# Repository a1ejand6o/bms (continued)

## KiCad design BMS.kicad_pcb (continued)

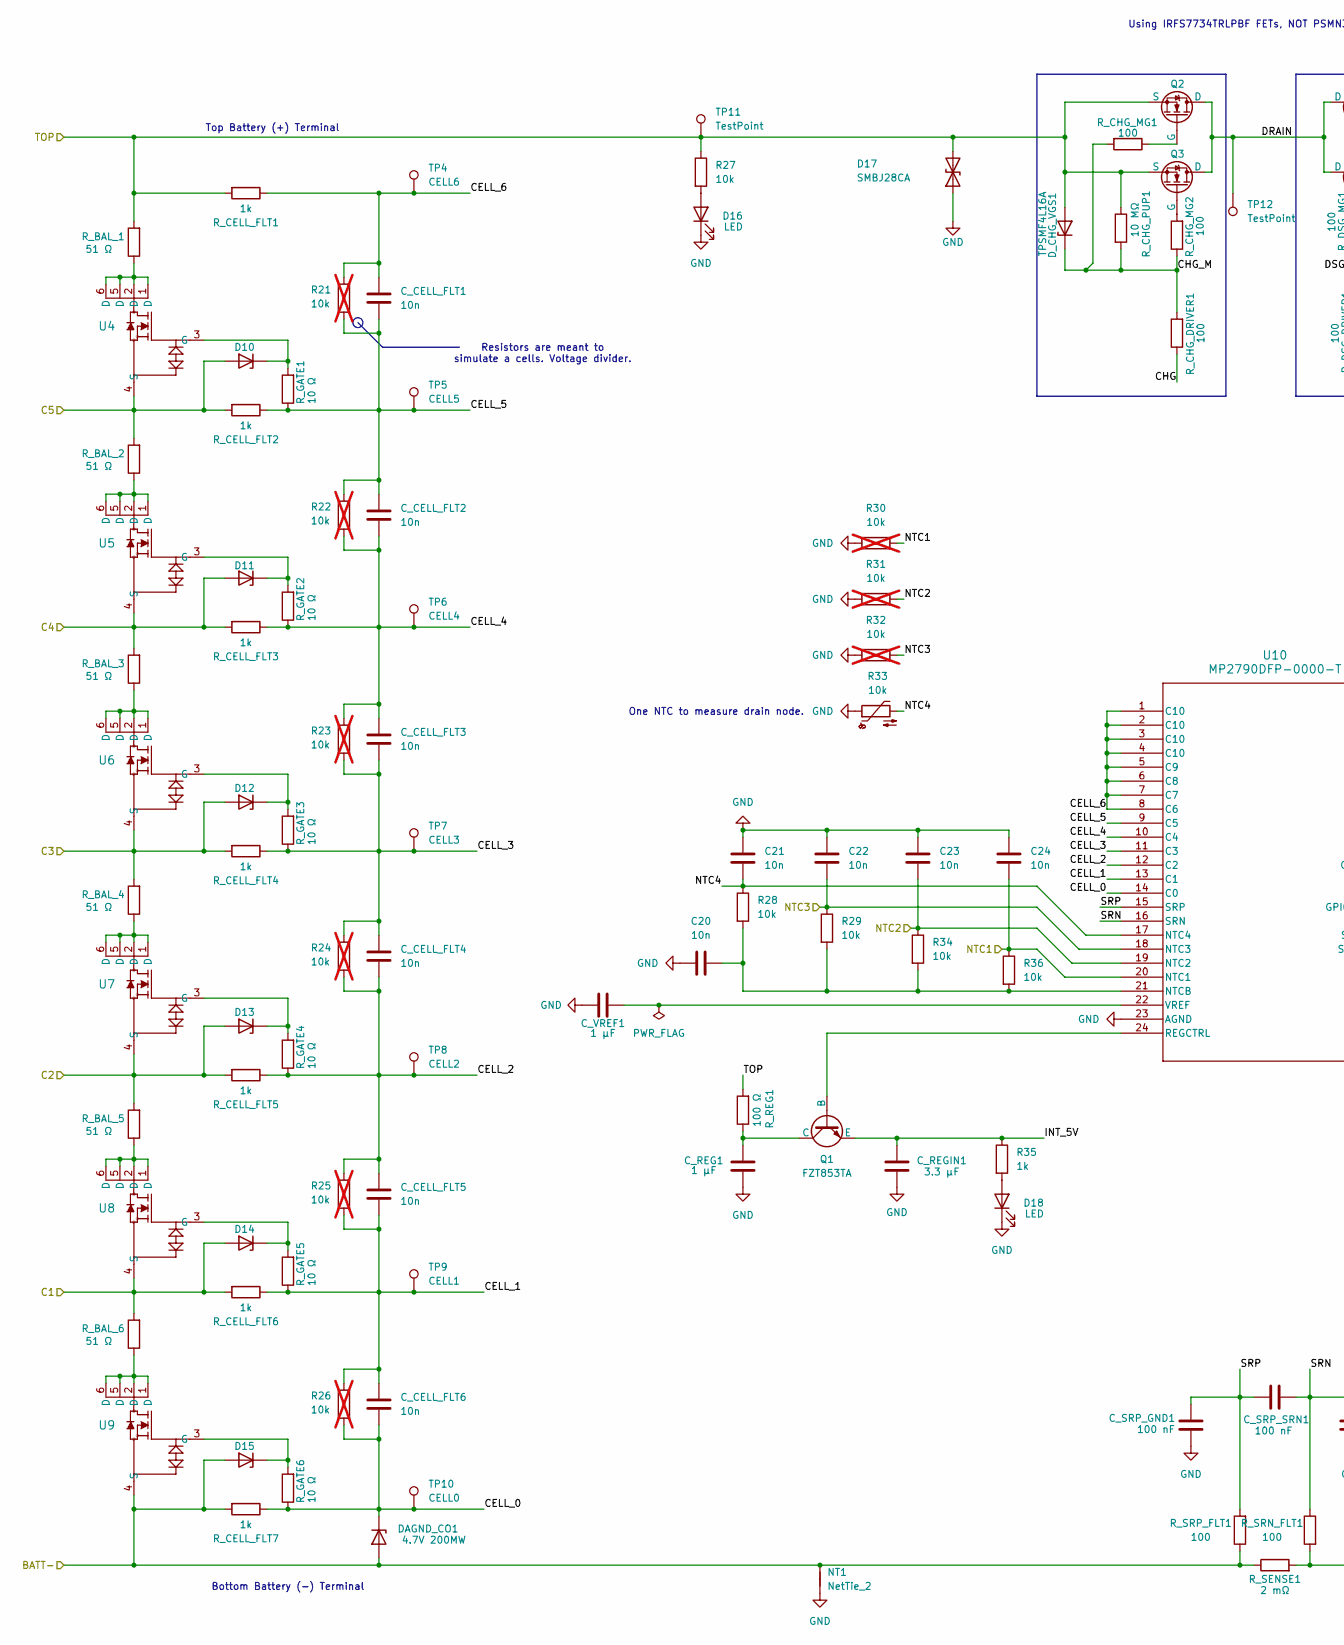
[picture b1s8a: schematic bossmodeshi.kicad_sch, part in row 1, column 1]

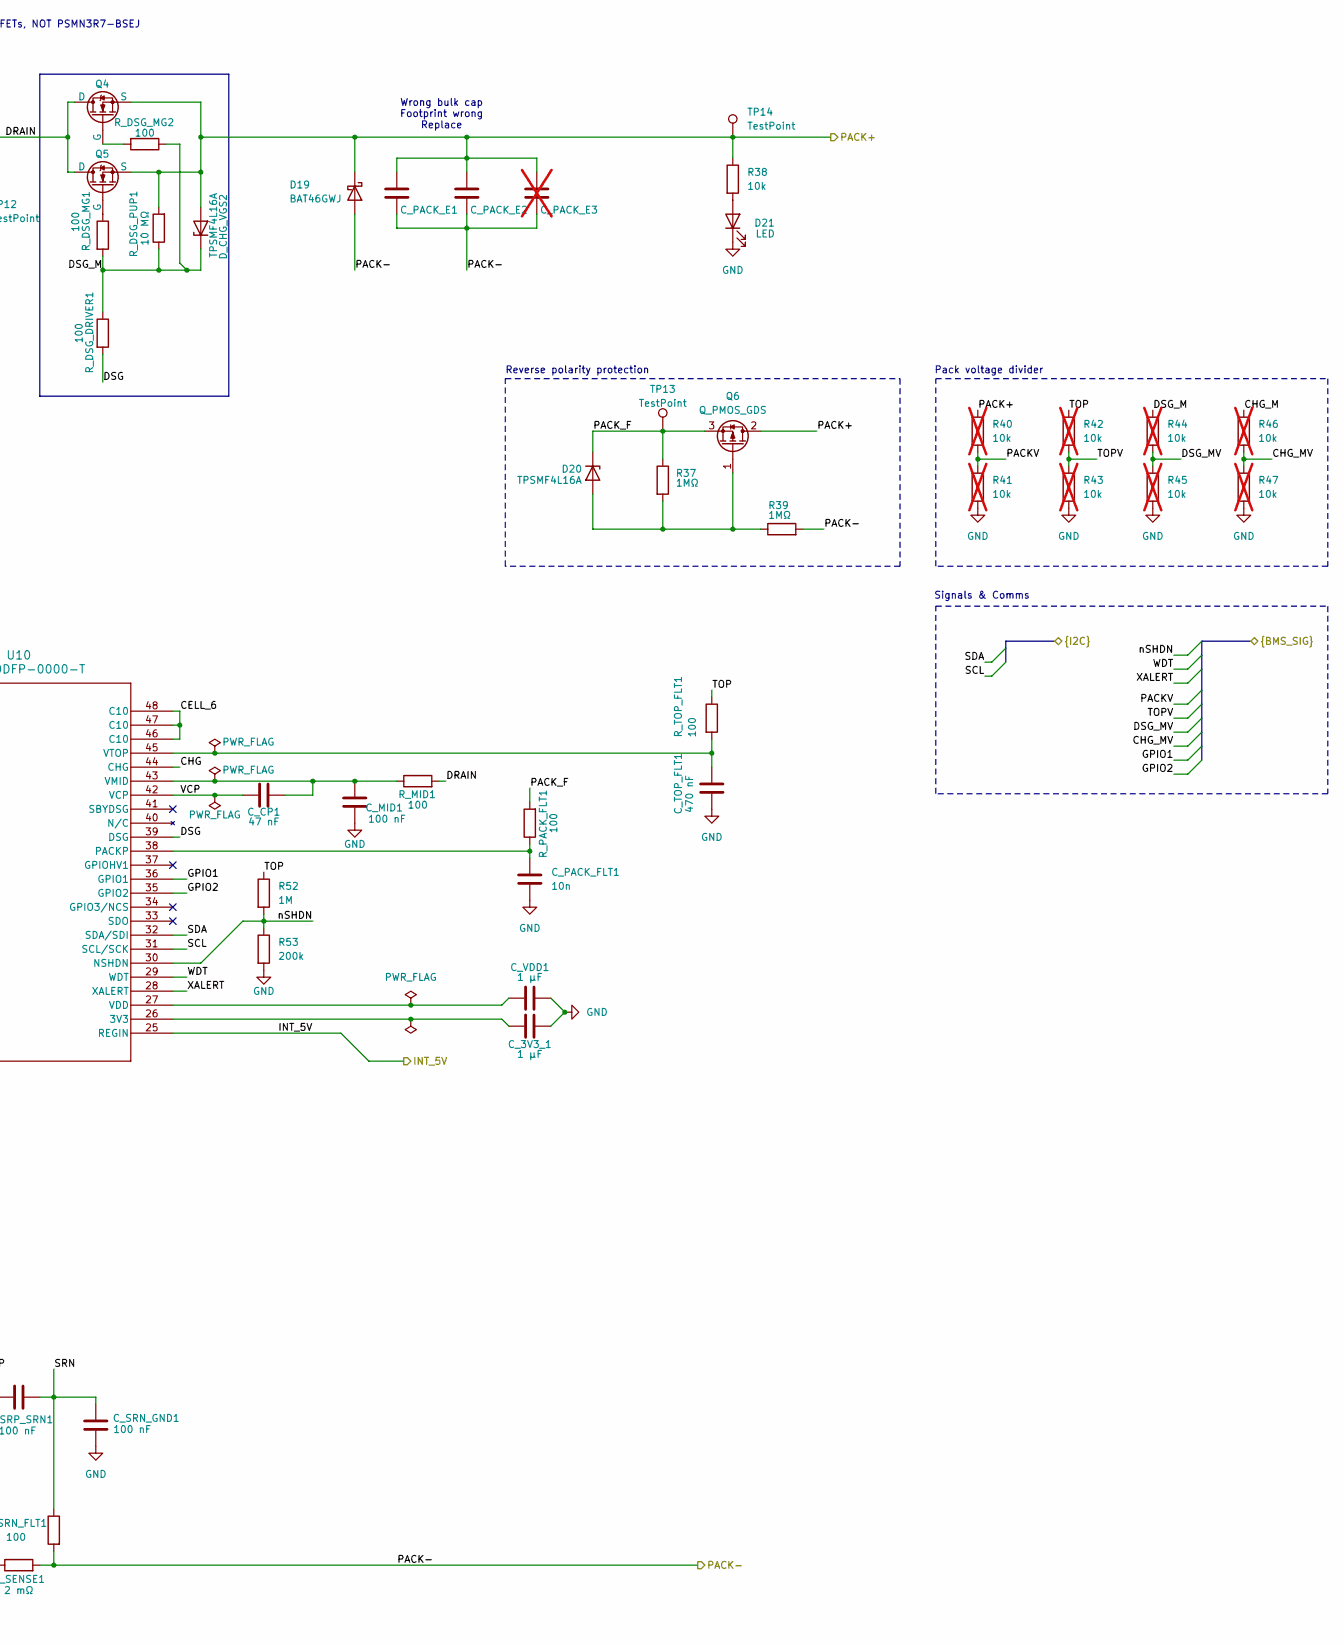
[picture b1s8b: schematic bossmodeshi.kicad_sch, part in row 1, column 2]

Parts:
C20, C21, C22, C23, C24: 10n; C_0603_1608Metric; Mfr P/N GRT1885C1E103FA02D
C_3V3_1: 1 μF; C_0603_1608Metric; Mfr P/N GCM188D71H105KE36J
C_CELL_FLT1, C_CELL_FLT2, C_CELL_FLT3, C_CELL_FLT4, C_CELL_FLT5, C_CELL_FLT6: 10n; C_0603_1608Metric; Mfr P/N GRT1885C1E103FA02D
C_CP1: 47 nF; C_0603_1608Metric; Mfr P/N CC0603JRX7R9BB473
C_MID1: 100 nF; C_0603_1608Metric; Mfr P/N CC0603JRX7R9BB104
C_PACK_E1, C_PACK_E2: C_1206_3216Metric
C_PACK_E3: C_1206_3216Metric; not fitted
C_PACK_FLT1: 10n; C_0603_1608Metric; Mfr P/N GRT1885C1E103FA02D
C_REG1: 1 μF; C_0603_1608Metric; Mfr P/N GCM188D71H105KE36J
C_REGIN1: 3.3 μF; C_0603_1608Metric; Mfr P/N C1608X5R1E335KT000E
C_SRN_GND1: 100 nF; C_0603_1608Metric; Mfr P/N CC0603JRX7R9BB104
C_SRP_GND1: 100 nF; C_0603_1608Metric; Mfr P/N CC0603JRX7R9BB104
C_SRP_SRN1: 100 nF; C_0603_1608Metric; Mfr P/N CC0603JRX7R9BB104
C_TOP_FLT1: 470 nF; C_0603_1608Metric; Mfr P/N CC0603KRX7R9BB474
C_VDD1: 1 μF; C_0603_1608Metric; Mfr P/N GCM188D71H105KE36J
C_VREF1: 1 μF; C_0603_1608Metric; Mfr P/N GCM188D71H105KE36J
D10, D11, D12, D13, D14, D15: PTVS5V0S1UR,115; Nexperia_CFP3_SOD-123W; Mfr P/N PTVS5V0S1UR,115
D16, D21: LED; LED_0603_1608Metric; Mfr P/N SML-310LTT86
D17: SMBJ28CA; D_SMB; Mfr P/N SMBJ28CA
D18: LED; LED_0603_1608Metric; Mfr P/N SML-E12P8WT86
D19: BAT46GWJ; D_SOD-123; Mfr P/N BAT46W-E3-18
D20: TPSMF4L16A; Nexperia_CFP3_SOD-123W; Mfr P/N TPSMF4L16A
DAGND_CO1: 4.7V 200MW; D_SOD-323; Mfr P/N BZT52C4V7S-7-F
D_CHG_VGS1, D_CHG_VGS2: TPSMF4L16A; Nexperia_CFP3_SOD-123W; Mfr P/N TPSMF4L16A
NT1: NetTie_2; NetTie-2_SMD_Pad2.0mm
Q1: FZT853TA; SOT230P700X185-4N; Mfr P/N FZT853TA
Q2, Q3, Q4, Q5: PSMN3R7-100BSE; TO-263-2; Mfr P/N PSMN3R7-100BSEJ
Q6: Q_PMOS_GDS; SOT-23; Mfr P/N SI01P10-TP
R21, R22, R23, R24, R25, R26, R40, R41, R42, R43, R44, R45, R46, R47: 10k; R_0603_1608Metric; Mfr P/N RC0603FR-0710KL; not fitted
R27, R28, R29, R34, R36, R38: 10k; R_0603_1608Metric; Mfr P/N RC0603FR-0710KL
R30, R31, R32: 10k; R_0603_1608Metric; not fitted
R33: 10k; R_0603_1608Metric; Mfr P/N NTCS0603E3103FLT
R35: 1k; R_0603_1608Metric; Mfr P/N AC0603FR-071KL
R37, R39: 1MΩ; R_0603_1608Metric; Mfr P/N RC0603FR-071ML
R52: 1M; R_0603_1608Metric; Mfr P/N 0603WAF1004T5E
R53: 200k; R_0603_1608Metric; Mfr P/N 0603WAF2003T5E
R_BAL_1, R_BAL_2, R_BAL_3, R_BAL_4, R_BAL_5, R_BAL_6: 51 Ω; R_1206_3216Metric; Mfr P/N SR1206FR-7W51RL
R_CELL_FLT1, R_CELL_FLT2, R_CELL_FLT3, R_CELL_FLT4, R_CELL_FLT5, R_CELL_FLT6, R_CELL_FLT7: 1k; R_0603_1608Metric; Mfr P/N AC0603FR-071KL
R_CHG_DRIVER1: 100; R_0603_1608Metric; Mfr P/N CRCW0603100RFKEAHP
R_CHG_MG1, R_CHG_MG2: 100; R_0603_1608Metric; Mfr P/N CRCW0603100RFKEAHP
R_CHG_PUP1: 10 MΩ; R_0603_1608Metric; Mfr P/N 0603WAF1005T5E
R_DSG_DRIVER1: 100; R_0603_1608Metric; Mfr P/N CRCW0603100RFKEAHP
R_DSG_MG1, R_DSG_MG2: 100; R_0603_1608Metric; Mfr P/N CRCW0603100RFKEAHP
R_DSG_PUP1: 10 MΩ; R_0603_1608Metric; Mfr P/N 0603WAF1005T5E
R_GATE1, R_GATE2, R_GATE3, R_GATE4, R_GATE5, R_GATE6: 10 Ω; R_0603_1608Metric; Mfr P/N CRCW060310R0FKEAHP
R_MID1: 100; R_0603_1608Metric; Mfr P/N CRCW0603100RFKEAHP
R_PACK_FLT1: 100; R_0603_1608Metric; Mfr P/N CRCW0603100RFKEAHP
R_REG1: 100 Ω; R_2512_6332Metric; Mfr P/N 25121WJ0101T4E
R_SENSE1: 2 mΩ; R_2512_6332Metric; Mfr P/N PA2512FKE7W0R002E
R_SRN_FLT1: 100; R_0603_1608Metric; Mfr P/N CRCW0603100RFKEAHP
R_SRP_FLT1: 100; R_0603_1608Metric; Mfr P/N CRCW0603100RFKEAHP
R_TOP_FLT1: 100; R_0603_1608Metric; Mfr P/N CRCW0603100RFKEAHP
TP4: CELL6; Harwin TP; Mfr P/N S2761-46R
TP5: CELL5; Harwin TP; Mfr P/N S2761-46R
TP6: CELL4; Harwin TP; Mfr P/N S2761-46R
TP7: CELL3; Harwin TP; Mfr P/N S2761-46R
TP8: CELL2; Harwin TP; Mfr P/N S2761-46R
TP9: CELL1; Harwin TP; Mfr P/N S2761-46R
TP10: CELL0; Harwin TP; Mfr P/N S2761-46R
TP11, TP12, TP13, TP14: TestPoint; Harwin TP; Mfr P/N S2761-46R
U4, U5, U6, U7, U8, U9: SQ1464EEH-T1_GE3; SC_4EEH-T1_GE3_VIS; Mfr P/N SQ1464EEH-T1_GE3
U10: MP2790DFP-0000-T; TQFP-48_MP2790_MNP; Mfr P/N MP2790DFP-0000-T

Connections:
/main/BMS/BATT-: D15.2 (A), DAGND_CO1.2 (A), NT1.2, R_CELL_FLT7.2, R_SENSE1.1, R_SRP_FLT1.1, U9.4 (S); also elsewhere on the board
/main/BMS/C1: D14.2 (A), R_BAL_6.2, R_CELL_FLT6.2, U8.4 (S); also elsewhere on the board
/main/BMS/C2: D13.2 (A), R_BAL_5.2, R_CELL_FLT5.2, U7.4 (S); also elsewhere on the board
/main/BMS/C3: D12.2 (A), R_BAL_4.2, R_CELL_FLT4.2, U6.4 (S); also elsewhere on the board
/main/BMS/C4: D11.2 (A), R_BAL_3.2, R_CELL_FLT3.2, U5.4 (S); also elsewhere on the board
/main/BMS/C5: D10.2 (A), R_BAL_2.2, R_CELL_FLT2.2, U4.4 (S); also elsewhere on the board
/main/BMS/CELL_0: C_CELL_FLT6.2, DAGND_CO1.1 (K), R26.2, R_CELL_FLT7.1, R_GATE6.1, TP10.1, U10.14 (C0)
/main/BMS/CELL_1: C_CELL_FLT5.2, C_CELL_FLT6.1, R25.2, R26.1, R_CELL_FLT6.1, R_GATE5.1, TP9.1, U10.13 (C1)
/main/BMS/CELL_2: C_CELL_FLT4.2, C_CELL_FLT5.1, R24.2, R25.1, R_CELL_FLT5.1, R_GATE4.1, TP8.1, U10.12 (C2)
/main/BMS/CELL_3: C_CELL_FLT3.2, C_CELL_FLT4.1, R23.2, R24.1, R_CELL_FLT4.1, R_GATE3.1, TP7.1, U10.11 (C3)
/main/BMS/CELL_4: C_CELL_FLT2.2, C_CELL_FLT3.1, R22.2, R23.1, R_CELL_FLT3.1, R_GATE2.1, TP6.1, U10.10 (C4)
/main/BMS/CELL_5: C_CELL_FLT1.2, C_CELL_FLT2.1, R21.2, R22.1, R_CELL_FLT2.1, R_GATE1.1, TP5.1, U10.9 (C5)
/main/BMS/CELL_6: C_CELL_FLT1.1, R21.1, R_CELL_FLT1.1, TP4.1, U10.1 (C10), U10.2 (C10), U10.3 (C10), U10.4 (C10), U10.5 (C9), U10.6 (C8), U10.7 (C7), U10.8 (C6), U10.46 (C10), U10.47 (C10), U10.48 (C10)
/main/BMS/CHG: R_CHG_DRIVER1.1, U10.44 (CHG)
/main/BMS/CHG_M: D_CHG_VGS1.1 (K), R46.1, R_CHG_DRIVER1.2, R_CHG_MG1.2, R_CHG_MG2.1, R_CHG_PUP1.2
/main/BMS/DRAIN: Q2.1 (D), Q3.1 (D), Q4.1 (D), Q5.1 (D), R_MID1.2, TP12.1
/main/BMS/DSG: R_DSG_DRIVER1.2, U10.39 (DSG)
/main/BMS/DSG_M: D_CHG_VGS2.1 (K), R44.1, R_DSG_DRIVER1.1, R_DSG_MG1.2, R_DSG_MG2.1, R_DSG_PUP1.1
/main/BMS/NTC1: C24.1, R30.2, R36.1, U10.20 (NTC1); also elsewhere on the board
/main/BMS/NTC2: C23.1, R31.2, R34.1, U10.19 (NTC2); also elsewhere on the board
/main/BMS/NTC3: C22.1, R29.1, R32.2, U10.18 (NTC3); also elsewhere on the board
/main/BMS/NTC4: C21.2, R28.1, R33.2, U10.17 (NTC4)
/main/BMS/PACK-: C_PACK_E1.2, C_PACK_E2.2, C_PACK_E3.2, D19.2 (A), R39.2, R_SENSE1.2, R_SRN_FLT1.2; also elsewhere on the board
/main/BMS/PACK_F: D20.1 (K), Q6.3 (S), R37.1, R_PACK_FLT1.2, TP13.1
/main/BMS/SCL: U10.31 (SCL/SCK); also elsewhere on the board
/main/BMS/SDA: U10.32 (SDA/SDI); also elsewhere on the board
/main/BMS/SRN: C_SRN_GND1.2, C_SRP_SRN1.1, R_SRN_FLT1.1, U10.16 (SRN)
/main/BMS/SRP: C_SRP_GND1.1, C_SRP_SRN1.2, R_SRP_FLT1.2, U10.15 (SRP)
/main/BMS/TOP: D17.2 (A2), D_CHG_VGS1.2 (A), Q2.3 (S), Q3.3 (S), R27.1, R42.1, R52.1, R_BAL_1.2, R_CELL_FLT1.2, R_CHG_PUP1.1, R_REG1.2, R_TOP_FLT1.1, TP11.1; also elsewhere on the board
/main/BMS/VCP: C_CP1.1, U10.42 (VCP)
/main/GPIO1: U10.36 (GPIO1); also elsewhere on the board
/main/GPIO2: U10.35 (GPIO2); also elsewhere on the board
/main/INT_5V: C_REGIN1.2, Q1.3 (E), R35.1, U10.25 (REGIN); also elsewhere on the board
/main/PACK+: C_PACK_E1.1, C_PACK_E2.1, C_PACK_E3.1, D19.1 (K), D_CHG_VGS2.2 (A), Q4.3 (S), Q5.3 (S), Q6.2 (D), R38.1, R40.1, R_DSG_PUP1.2, TP14.1; also elsewhere on the board
/main/WDT: U10.29 (WDT); also elsewhere on the board
/main/XALERT: U10.28 (XALERT); also elsewhere on the board
/main/nSHDN: R52.2, R53.1, U10.30 (NSHDN); also elsewhere on the board
GND: C20.1, C21.1, C22.2, C23.2, C24.2, C_3V3_1.1, C_MID1.2, C_PACK_FLT1.2, C_REG1.2, C_REGIN1.1, C_SRN_GND1.1, C_SRP_GND1.2, C_TOP_FLT1.2, C_VDD1.2, C_VREF1.2, D16.1 (K), D17.1 (A1), D18.1 (K), D21.1 (K), NT1.1, R30.1, R31.1, R32.1, R33.1, R41.2, R43.2, R45.2, R47.2, R53.2, U10.23 (AGND); also elsewhere on the board
unnamed: D10.1 (K), R_GATE1.2, U4.3 (G)
unnamed: D11.1 (K), R_GATE2.2, U5.3 (G)
unnamed: D12.1 (K), R_GATE3.2, U6.3 (G)
unnamed: D13.1 (K), R_GATE4.2, U7.3 (G)
unnamed: D14.1 (K), R_GATE5.2, U8.3 (G)
unnamed: D15.1 (K), R_GATE6.2, U9.3 (G)
unnamed: D16.2 (A), R27.2
unnamed: D18.2 (A), R35.2
unnamed: D20.2 (A), Q6.1 (G), R37.2, R39.1
unnamed: D21.2 (A), R38.2
unnamed: Q1.2 (B), U10.24 (REGCTRL)
unnamed: C_REG1.1, Q1.1 (C), R_REG1.1
unnamed: Q2.2 (G), R_CHG_MG1.1
unnamed: Q3.2 (G), R_CHG_MG2.2
unnamed: Q4.2 (G), R_DSG_MG2.2
unnamed: Q5.2 (G), R_DSG_MG1.1
unnamed: R40.2, R41.1
unnamed: R42.2, R43.1
unnamed: R44.2, R45.1
unnamed: R46.2, R47.1
unnamed: R_BAL_1.1, U4.1 (D), U4.2 (D), U4.5 (D), U4.6 (D)
unnamed: R_BAL_2.1, U5.1 (D), U5.2 (D), U5.5 (D), U5.6 (D)
unnamed: R_BAL_3.1, U6.1 (D), U6.2 (D), U6.5 (D), U6.6 (D)
unnamed: R_BAL_4.1, U7.1 (D), U7.2 (D), U7.5 (D), U7.6 (D)
unnamed: R_BAL_5.1, U8.1 (D), U8.2 (D), U8.5 (D), U8.6 (D)
unnamed: R_BAL_6.1, U9.1 (D), U9.2 (D), U9.5 (D), U9.6 (D)
unnamed: C_3V3_1.2, U10.26 (3V3)
unnamed: C20.2, R28.2, R29.2, R34.2, R36.2, U10.21 (NTCB)
unnamed: C_PACK_FLT1.1, R_PACK_FLT1.1, U10.38 (PACKP)
unnamed: C_VDD1.1, U10.27 (VDD)
unnamed: C_CP1.2, C_MID1.1, R_MID1.1, U10.43 (VMID)
unnamed: C_VREF1.1, U10.22 (VREF)
unnamed: C_TOP_FLT1.1, R_TOP_FLT1.2, U10.45 (VTOP)

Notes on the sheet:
Using IRFS7734TRLPBF FETs, NOT PSMN3R7-BSEJ
Resistors are meant to simulate a cells. Voltage divider.
Footprint wrong Replace
Reverse polarity protection
Pack voltage divider
Top Battery (+) Terminal
Wrong bulk cap
Signals & Comms
Bottom Battery (-) Terminal
One NTC to measure drain node.

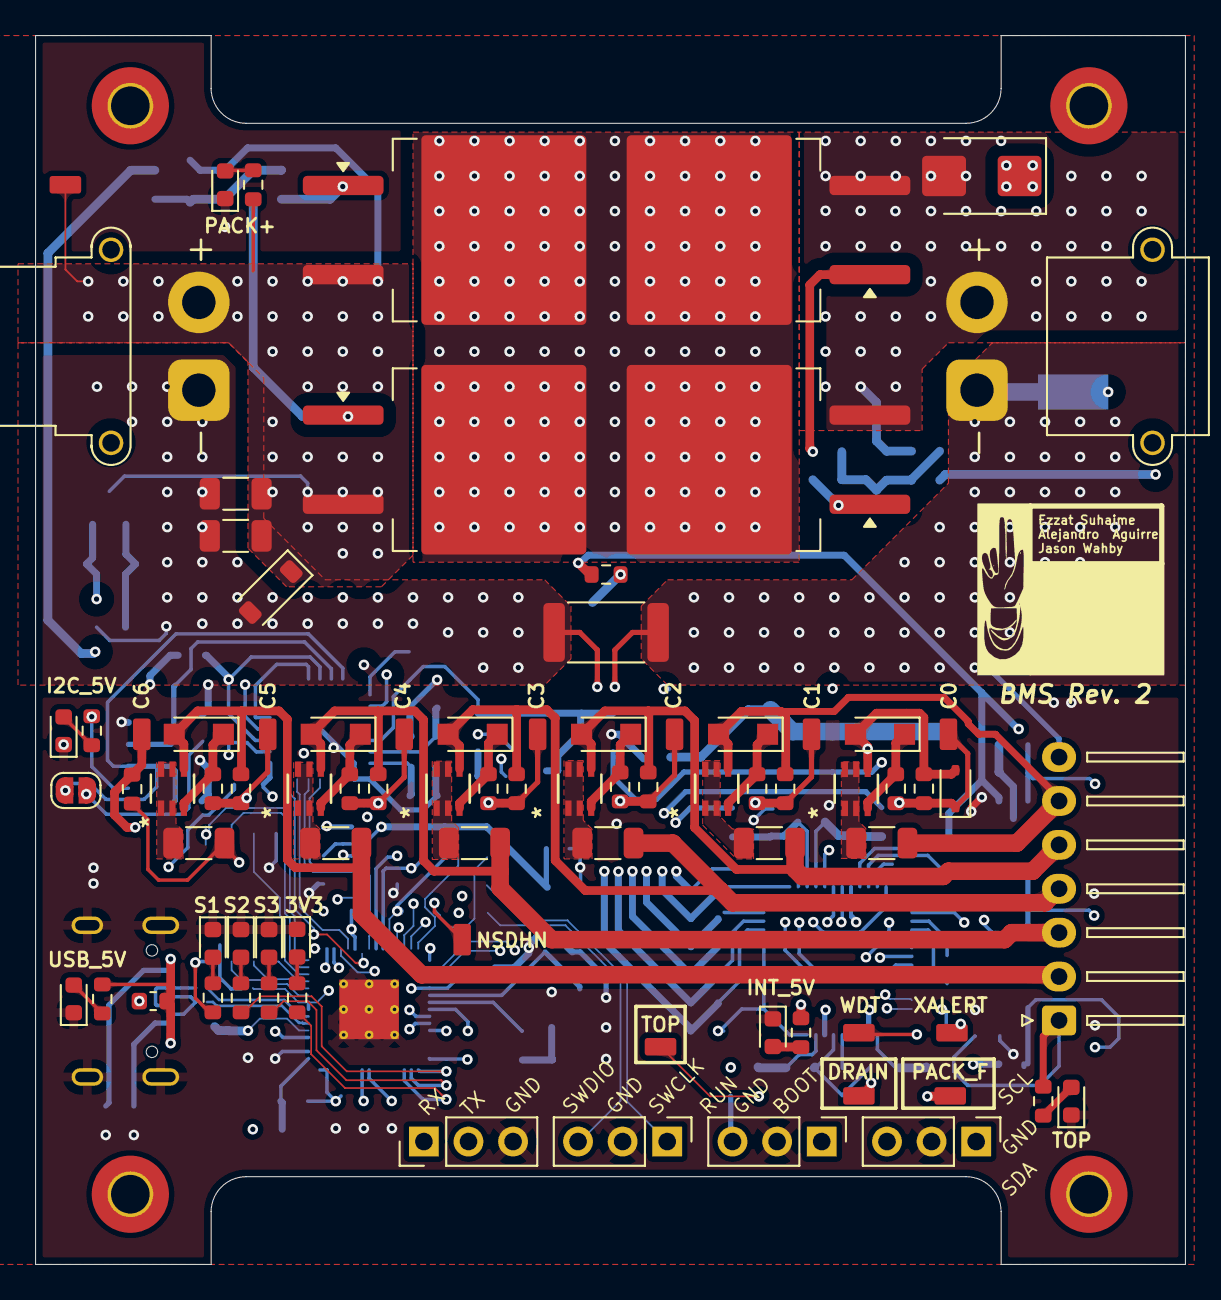
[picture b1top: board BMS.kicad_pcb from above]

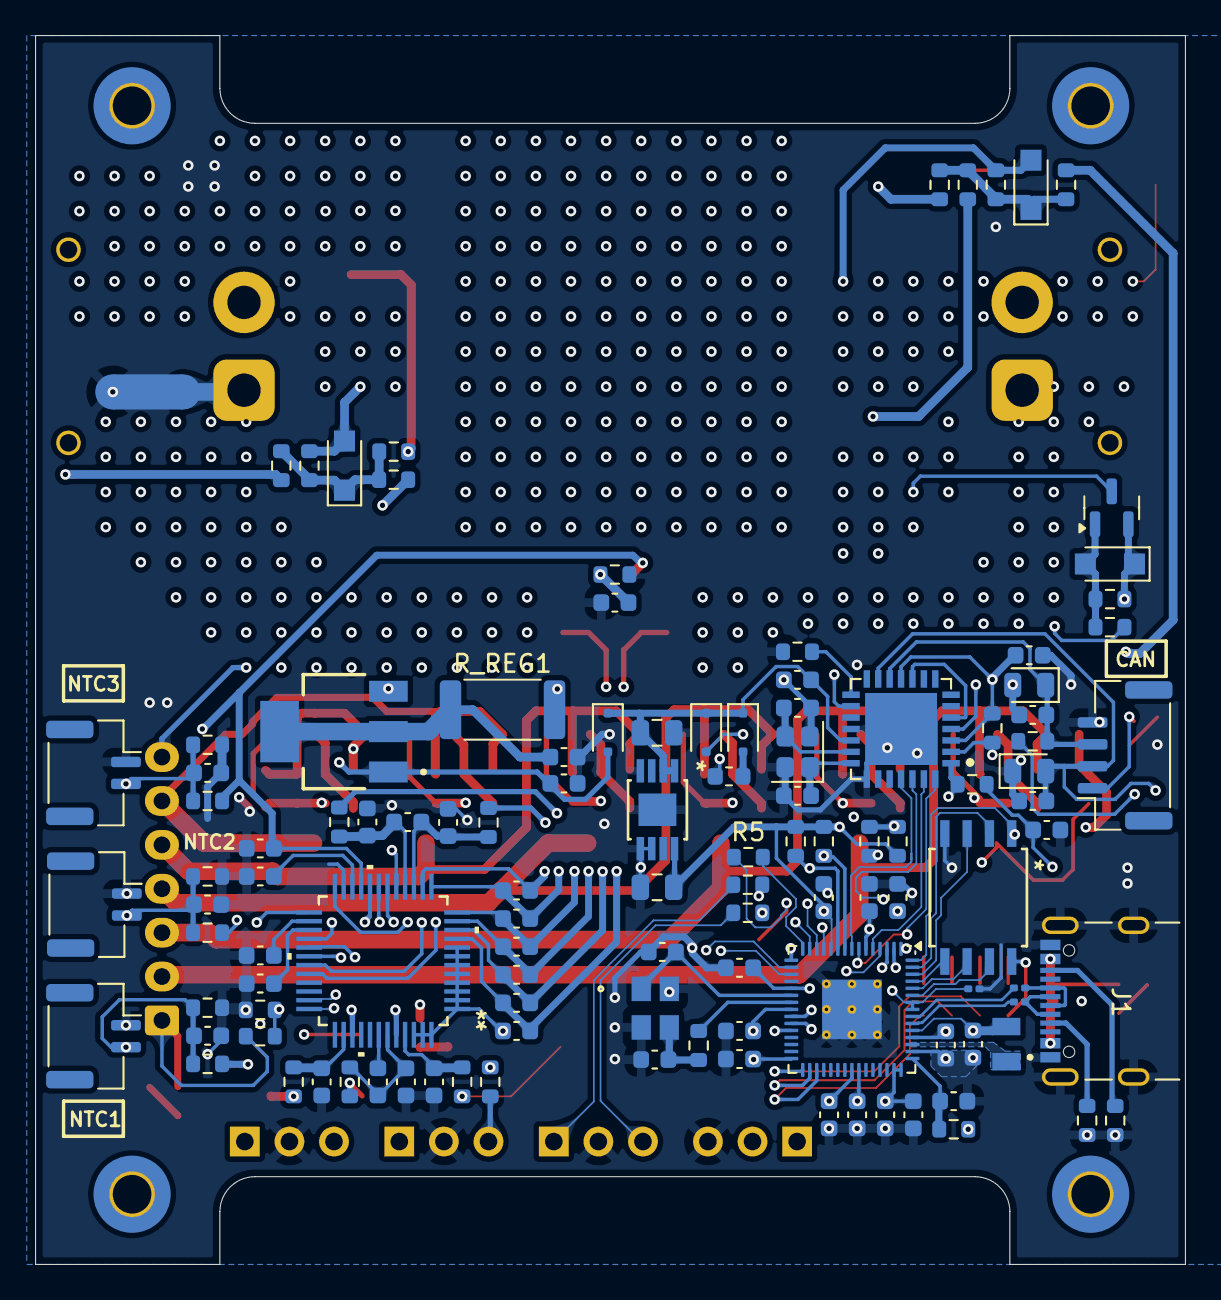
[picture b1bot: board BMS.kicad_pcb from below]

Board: 6 copper layers, 65.5 x 70.0 mm, 203 parts (116 on the bottom side), 124 nets.

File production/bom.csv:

Designator,Footprint,Quantity,Value,LCSC Part #
"C1, C10, C11, C13, C14, C2, C27, C28, C3, C4, C5, C6, C_MID1, C_SRN_GND1, C_SRP_GND1, C_SRP_SRN1",0603,16,100 nF,
C12,0201,1,100 nF,
"C15, C16, C17, C9",0603,4,4.7u,
"C18, C19",0805,2,10uF,
"C20, C21, C22, C23, C24, C_CELL_FLT1, C_CELL_FLT2, C_CELL_FLT3, C_CELL_FLT4, C_CELL_FLT5, C_CELL_FLT6, C_PACK_FLT1",0603,12,10n,
C25,0603,1,18pF,C1647
C26,0603,1,18pF,
"C29, C30",0603,2,47pF,C1671
"C7, C8",0603,2,15p,
"C_3V3_1, C_REG1, C_VDD1, C_VREF1",0603,4,1 μF,
C_CP1,0603,1,47 nF,
C_REGIN1,0603,1,3.3 μF,
C_TOP_FLT1,0603,1,470 nF,
"D1, D16, D18, D2, D21, D3, D4, D5, D9",0603,9,LED,
"D10, D11, D12, D13, D14, D15",Nexperia_CFP3_SOD-123W,6,"PTVS5V0S1UR,115",
D17,D_SMB,1,TPSMB28CA-VR,
D19,D_SOD-123,1,BAT46GWJ,
"D20, D_CHG_VGS1, D_CHG_VGS2",Nexperia_CFP3_SOD-123W,3,TPSMF4L16A,
"D22, D23",0805,2,AQ24C-01FTG,C315918
"D6, D7, D8",D_SOD-323F,3,SS16HE,
DAGND_CO1,D_SOD-323,1,4.7V 200MW,
"FB1, FB2",0603,2,120Ω@100MHz,
J1,SAMESKY_UJ20-C-H-G-SMT-1-P16-TR,1,UJ20-C-H-G-SMT-1-P16-TR,
"J10, J11, J12",JST_GH_SM02B-GHS-TB_1x02-1MP_P1.25mm_Horizontal,3,Conn_01x02_Pin,
J2,AMASS_XT30PW-F_1x02_P2.50mm_Horizontal,1,Conn_01x02_Socket,
"J3, J5, J6, J7",PinHeader_1x03_P2.54mm_Vertical,4,Conn_01x03_Socket,
J4,JST_GH_SM04B-GHS-TB_1x04-1MP_P1.25mm_Horizontal,1,Conn_01x04_Socket,
J8,JST_XH_S7B-XH-A-1_1x07_P2.50mm_Horizontal,1,Conn_01x07_Pin,
J9,AMASS_XT30PW-M_1x02_P2.50mm_Horizontal,1,Conn_01x02_Pin,
L1,rp_inductor,1,3.3u,
Q1,SOT230P700X185-4N,1,FZT853TA,
"Q2, Q3, Q4, Q5",TO-263-2,4,PSMN3R7-100BSE,
Q6,SOT-23,1,Q_PMOS_GDS,
"R1, R2",0603,2,5.1k,
"R10, R12, R13, R20, R3, R35, R4, R_CELL_FLT1, R_CELL_FLT2, R_CELL_FLT3, R_CELL_FLT4, R_CELL_FLT5, R_CELL_FLT6, R_CELL_FLT7",0603,14,1k,
"R11, R27, R28, R29, R33, R34, R36, R38, R5, R8, R9",0603,11,10k,
"R14, R15",0201,2,27,
"R16, R18, R19",0603,3,470,
R17,0603,1,33,
"R37, R39",0603,2,1MΩ,
"R48, R49, R50",0603,3,10K,C4037161
R51,0603,1,120,C22787
R52,0603,1,1M,
R53,0603,1,200k,
"R6, R7, R_CHG_DRIVER1, R_CHG_MG1, R_CHG_MG2, R_DSG_DRIVER1, R_DSG_MG1, R_DSG_MG2, R_MID1, R_PACK_FLT1, R_SRN_FLT1, R_SRP_FLT1, R_TOP_FLT1",0603,13,100,
"R_BAL_1, R_BAL_2, R_BAL_3, R_BAL_4, R_BAL_5, R_BAL_6",1206,6,51 Ω,
"R_CHG_PUP1, R_DSG_PUP1",0603,2,10 MΩ,
"R_GATE1, R_GATE2, R_GATE3, R_GATE4, R_GATE5, R_GATE6",0603,6,10 Ω,
R_REG1,2512,1,100 Ω,
R_SENSE1,2512,1,2 mΩ,
"TP1, TP11, TP12, TP13, TP14, TP2, TP3",Harwin TP,7,TestPoint,
TP10,Harwin TP,1,CELL0,
TP4,Harwin TP,1,CELL6,
TP5,Harwin TP,1,CELL5,
TP6,Harwin TP,1,CELL4,
TP7,Harwin TP,1,CELL3,
TP8,Harwin TP,1,CELL2,
TP9,Harwin TP,1,CELL1,
U1,SOIC-8_5P28X5P28_WIN,1,W25Q64JVSSIQ,
U10,TQFP-48_MP2790_MNP,1,MP2790DFP-0000-T,
U11,QFN-28L,1,MCP25625-E/ML,C481365
U2,QFN-60-1EP_7x7mm_P0.4mm_EP3.4x3.4mm_ThermalVias,1,RP2350A,
U3,VSSOP8_DGN_TEX,1,TPS7B8133QDGNRQ1,
"U4, U5, U6, U7, U8, U9",SC_4EEH-T1_GE3_VIS,6,SQ1464EEH-T1_GE3,
X1,ABM8-272-T3_ABR,1,ABM8-272-T3,
Y1,Crystal_SMD_2520-4Pin_2.5x2.0mm,1,16MHz 12pF,C426965

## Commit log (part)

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2025-10-14 Starting KiCad project
2025-10-20 almost completed scheamtic
2025-10-21 post solar meeting with ezzat
2025-10-25 almost done schematic
2025-10-29 Fixing and cleaning up schematic
2025-10-30 Reviewed and cleaned up schematic
2025-10-31 Finishing gate drive stuff
2025-11-03 Reorganized, added in LSW, and TC ports
2025-11-03 added resistors for thermistors
2025-11-12 Pushing
2025-11-12 small changes, nothing crazy
2025-11-18 added external mosfets
2025-11-18 mosfets added
2025-11-19 added footprints
2025-12-18 Adding in diodes and fixing circuit
2025-12-19 Dumb layout
2025-12-23 bms layout progress
2025-12-25 Working on microcontroller
2025-12-27 Updating schematic and adding in compnents to the PCB
2025-12-28 schematic progress
2026-01-02 Layed on board. Still need to route
2026-01-11 Adding proper grounding
2026-01-20 Lots of changfes
2026-01-21 Tweaks and production files
2026-01-28 Updating BOM
2026-02-26 Updating stuff
2026-03-02 Placement
2026-03-08 Doing placement
2026-03-08 Prelim placement done
2026-03-09 Did a lot of routing
2026-04-13 Working on routing
2026-04-20 reverse polarity protection
2026-04-20 Working on reverse polarity
2026-04-20 Adding in signals and cleaning up schematic
2026-04-23 Redoing layout
2026-05-01 prepaing for production
2026-05-02 Fixes
